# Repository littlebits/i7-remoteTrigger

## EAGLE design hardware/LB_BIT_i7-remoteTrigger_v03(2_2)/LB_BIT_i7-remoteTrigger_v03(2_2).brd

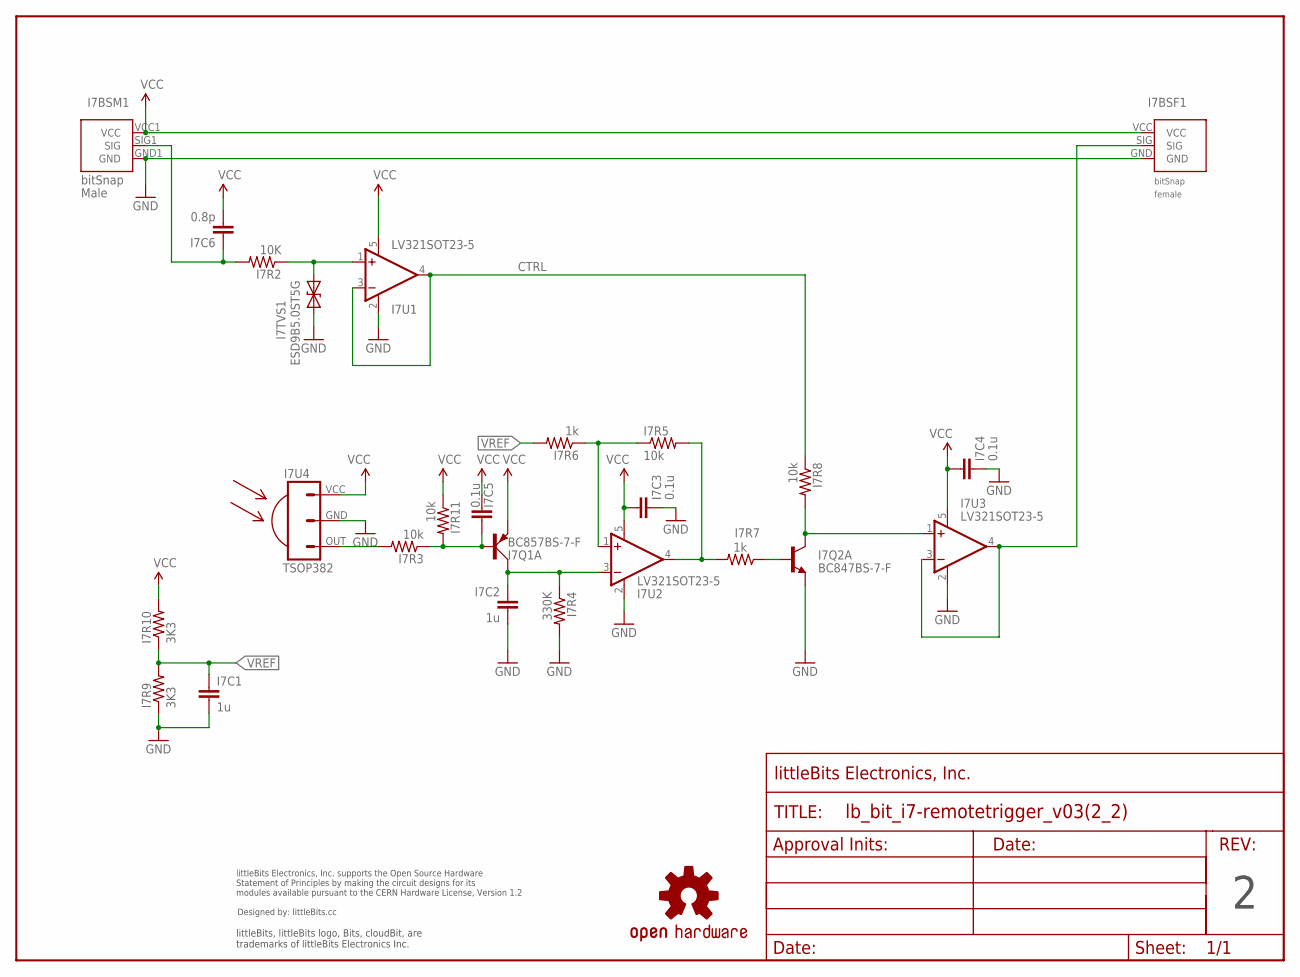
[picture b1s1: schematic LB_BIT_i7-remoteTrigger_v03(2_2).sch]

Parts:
I7BSF1: BITSNAP_V03_FEMALE
I7BSM1: BITSNAP_V03_MALE
I7C1, I7C2: 1u; CAP-0603
I7C3, I7C4, I7C5: 0.1u; CAP-0603
I7C6: 0.8p; CAP-0603
I7Q1: BC857BS-7-F; SOT-363_PHILLIPS
I7Q2: BC847BS-7-F; SOT-363_PHILLIPS
I7R2: 10K; RES-0603
I7R3, I7R5, I7R8, I7R11: 10k; RES-0603
I7R4: 330K; RES-0603
I7R6, I7R7: 1k; RES-0603
I7R9, I7R10: 3K3; RES-0603
I7TVS1: ESD9B5.0ST5G; SOD-923
I7U1, I7U2, I7U3: LV321SOT23-5; SOT23-5
I7U4: TSOP382; IR-RECEIVER-TSOP382-THRU-HOLE
U$2: OSHWCREDIT
U$3: OSHW-LOGOL; OSHW-LOGO-L
U$21: FRAME-LETTER-OHWOHW; FABDWG01-OHW

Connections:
CTRL: I7R8.1, I7U1.3 (-IN), I7U1.4 (OUT)
GND: I7BSF1.GND, I7BSM1.GND1 (GND), I7C1.2, I7C2.2, I7C3.1, I7C4.1, I7Q2.1 (E), I7R4.2, I7R9.1, I7TVS1.1 (A), I7U1.2 (V-), I7U2.2 (V-), I7U3.2 (V-), I7U4.GND
unnamed: I7R5.2, I7R7.2, I7U2.4 (OUT)
unnamed: I7C5.2, I7Q1.2 (B), I7R3.1, I7R11.2
unnamed: I7C2.1, I7Q1.6 (C), I7R4.1, I7U2.3 (-IN)
unnamed: I7R5.1, I7R6.1, I7U2.1 (+IN)
unnamed: I7Q2.2 (B), I7R7.1
unnamed: I7R3.2, I7U4.OUT
unnamed: I7Q2.6 (C), I7R8.2, I7U3.1 (+IN)
unnamed: I7R2.1, I7TVS1.2 (C), I7U1.1 (+IN)
unnamed: I7BSM1.SIG1 (SIG), I7C6.1, I7R2.2
unnamed: I7BSF1.SIG, I7U3.3 (-IN), I7U3.4 (OUT)
VCC: I7BSF1.VCC, I7BSM1.VCC1 (VCC), I7C3.2, I7C4.2, I7C5.1, I7C6.2, I7Q1.1 (E), I7R10.2, I7R11.1, I7U1.5 (V+), I7U2.5 (V+), I7U3.5 (V+), I7U4.VCC
VREF: I7C1.1, I7R6.2, I7R9.2, I7R10.1

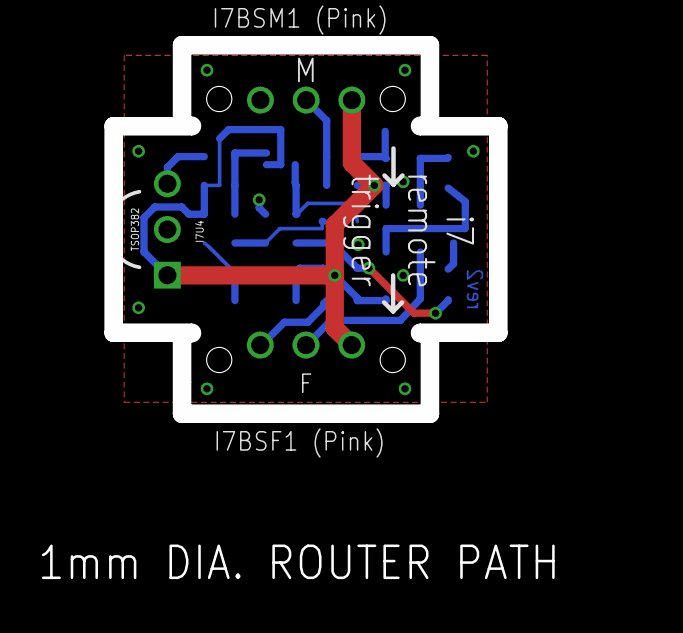
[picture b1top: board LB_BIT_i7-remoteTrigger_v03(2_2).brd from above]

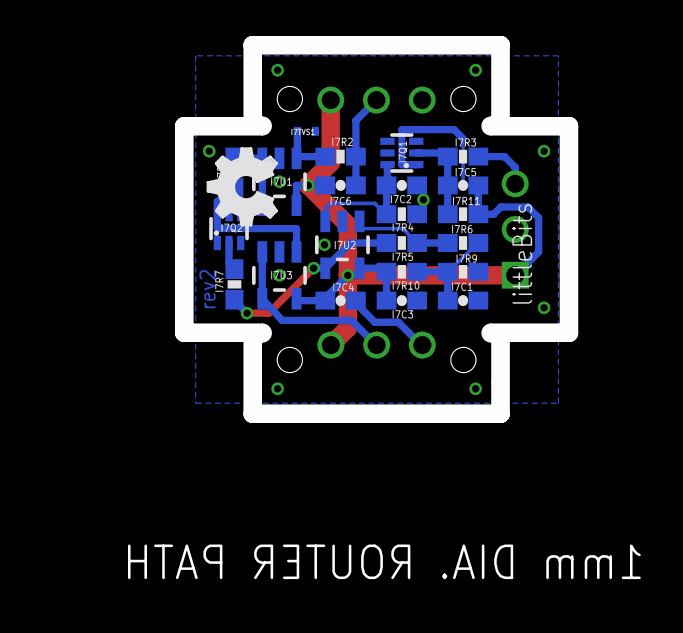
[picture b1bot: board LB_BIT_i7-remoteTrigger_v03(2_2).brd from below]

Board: 2 copper layers, 32.9 x 30.2 mm, 29 parts (22 on the bottom side), 14 nets.

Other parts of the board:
U$6: OSHW_FILLX150_NOTEXT

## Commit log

2014-11-12 First commit, added hardware files
2014-11-12 Added readme

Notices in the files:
parts and their libraries:
LITTLEBITS: modules available pursuant to the CERN Hardware License,
Version 1.2
LITTLEBITS: modules available pursuant to the CERN Hardware License, Version 1.2
